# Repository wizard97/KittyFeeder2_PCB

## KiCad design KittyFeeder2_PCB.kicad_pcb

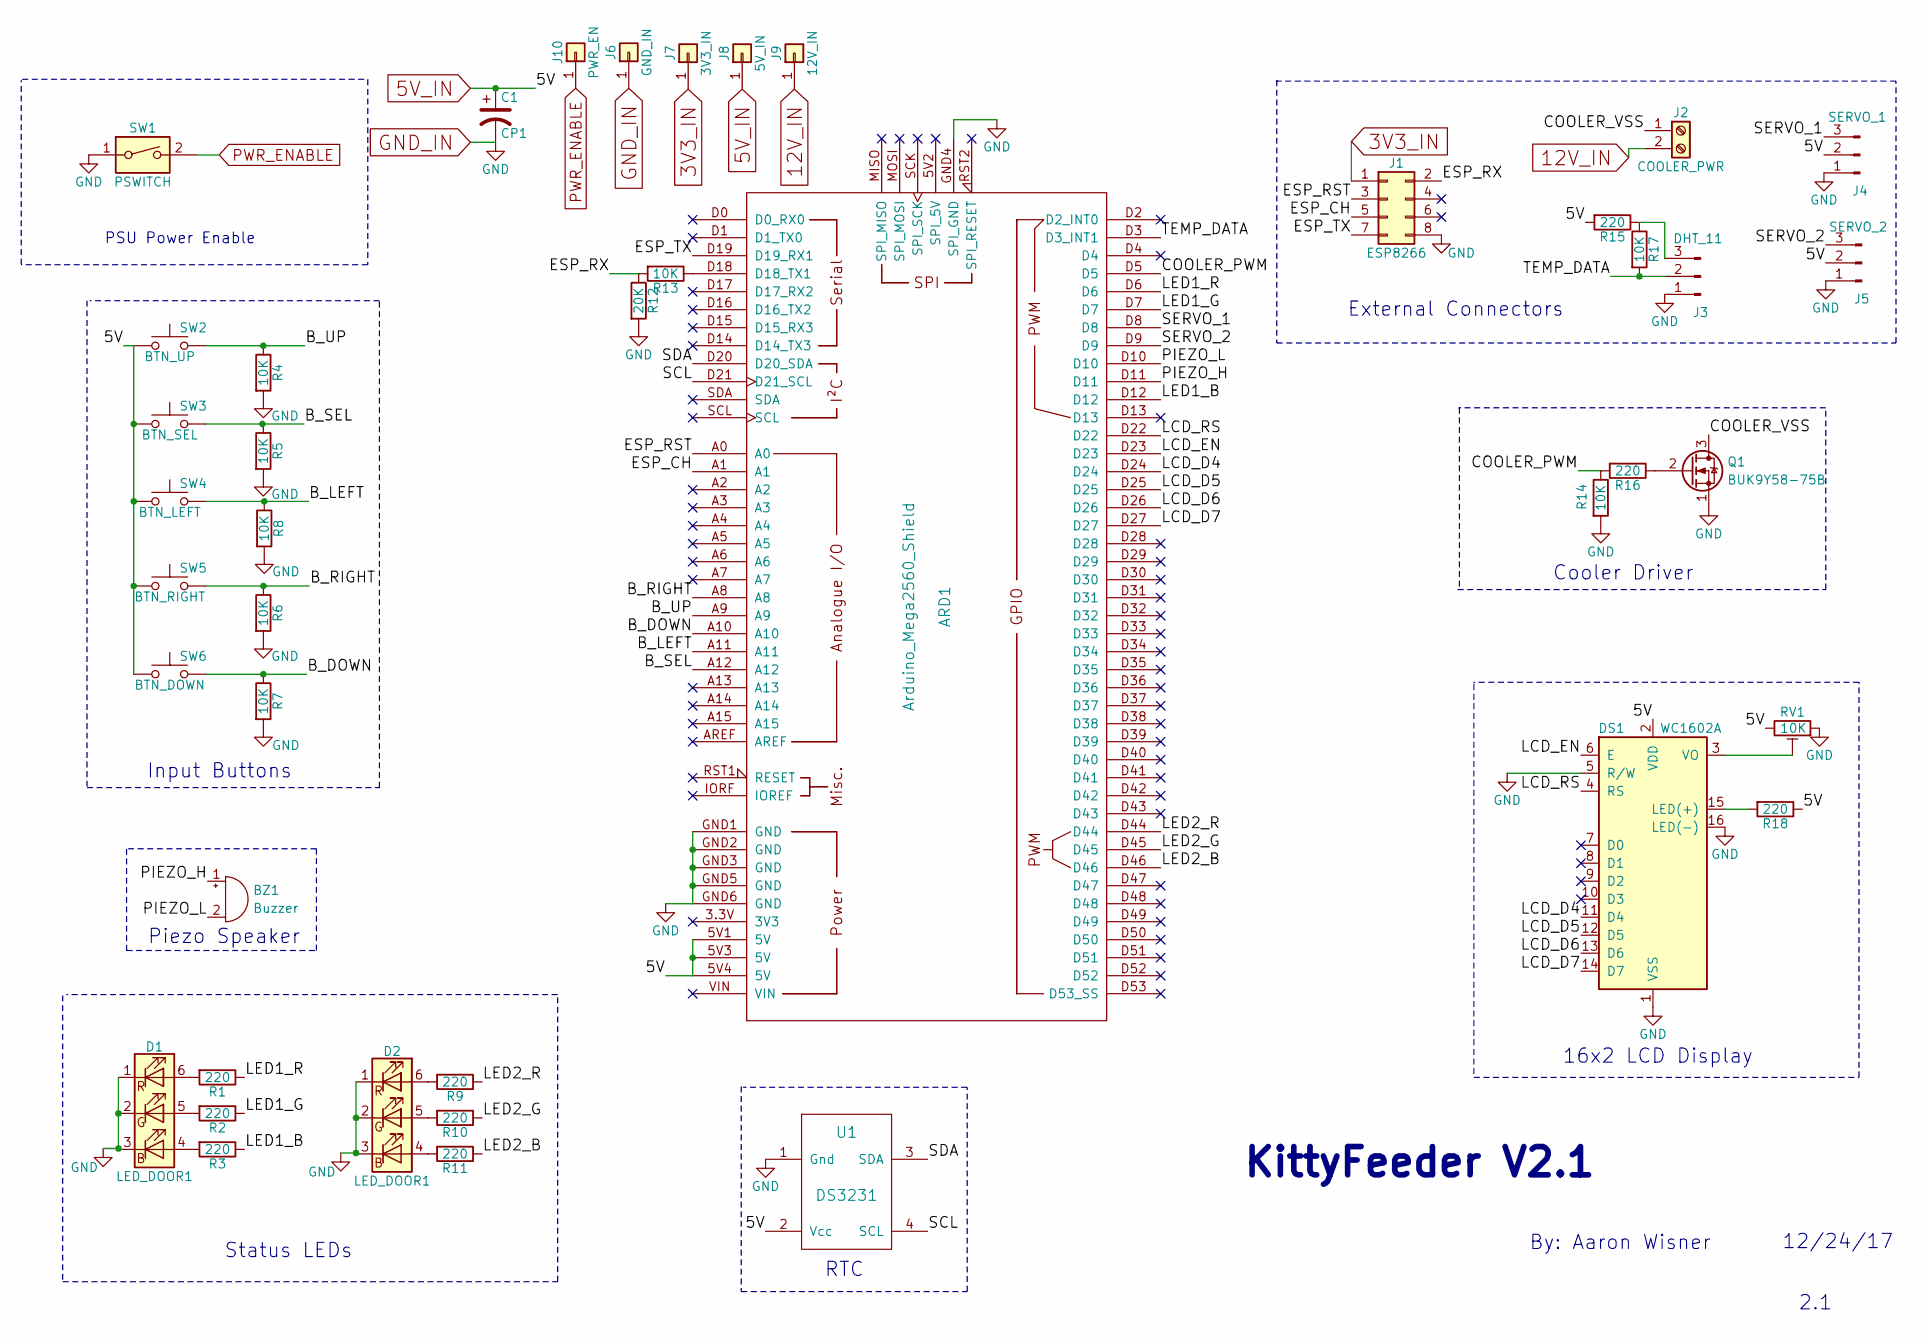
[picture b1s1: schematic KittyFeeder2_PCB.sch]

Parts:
ARD1: Arduino_Mega2560_Shield
BZ1: Buzzer; Buzzer_12x9.5RM7.6
C1: CP1; CP_Radial_D8.0mm_P2.50mm
D1, D2: LED_DOOR1; LED_RGB_PLCC-6
DS1: WC1602A
J1: ESP8266; Socket_Strip_Straight_2x04_Pitch2.54mm
J2: COOLER_PWR; TerminalBlock_Phoenix_MKDS1.5-2pol
J3: DHT_11; Socket_Strip_Straight_1x03_Pitch2.54mm
J4: SERVO_1; Socket_Strip_Straight_1x03_Pitch2.54mm
J5: SERVO_2; Socket_Strip_Straight_1x03_Pitch2.54mm
J6: GND_IN; SolderWirePad_4xSquare_2mmDrill
J7: 3V3_IN; SolderWirePad_single_2mmDrill
J8: 5V_IN; SolderWirePad_2x_2mmDrill
J9: 12V_IN; SolderWirePad_4xSquare_2mmDrill
J10: PWR_EN; SolderWirePad_4xSquare_2mmDrill
Q1: BUK9Y58-75B; SOT-669_LFPAK
R1, R2, R3, R9, R10, R11, R15, R16, R18: 220; R_0603
R4, R5, R6, R7, R8, R13, R14, R17: 10K; R_0603
R12: 20K; R_0603
RV1: 10K; Potentiometer_WirePads_Small
SW1: PSWITCH; Socket_Strip_Straight_1x02_Pitch2.54mm
SW2: BTN_UP; SW_PUSH-12mm
SW3: BTN_SEL; SW_PUSH-12mm
SW4: BTN_LEFT; SW_PUSH-12mm
SW5: BTN_RIGHT; SW_PUSH-12mm
SW6: BTN_DOWN; SW_PUSH-12mm
U1: DS3231; Socket_Strip_Straight_1x04_Pitch2.54mm

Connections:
3V3_IN: J1.1, J7.1
5V_IN: ARD1.5V1 (5V), ARD1.5V3 (5V), ARD1.5V4 (5V), C1.1, DS1.2 (VDD), J4.2, J5.2, J8.1, R15.2, R18.1, RV1.3, SW2.1, SW3.1, SW4.1, SW5.1, SW6.1, U1.2 (Vcc)
12V_IN: J2.2, J9.1
/B_DOWN: ARD1.A10, R7.1, SW6.2
/B_LEFT: ARD1.A11, R8.1, SW4.2
/B_RIGHT: ARD1.A8, R6.1, SW5.2
/B_SEL: ARD1.A12, R5.1, SW3.2
/B_UP: ARD1.A9, R4.1, SW2.2
/COOLER_PWM: ARD1.D5, R14.1, R16.2
/COOLER_VSS: J2.1, Q1.3 (D)
/ESP_CH: ARD1.A1, J1.5
/ESP_RST: ARD1.A0, J1.3
/ESP_RX: J1.2, R12.1, R13.2
/ESP_TX: ARD1.D19 (D19_RX1), J1.7
/LCD_D4: ARD1.D24, DS1.11 (D4)
/LCD_D5: ARD1.D25, DS1.12 (D5)
/LCD_D6: ARD1.D26, DS1.13 (D6)
/LCD_D7: ARD1.D27, DS1.14 (D7)
/LCD_EN: ARD1.D23, DS1.6 (E)
/LCD_RS: ARD1.D22, DS1.4 (RS)
/LED1_B: ARD1.D12, R3.1
/LED1_G: ARD1.D7, R2.1
/LED1_R: ARD1.D6, R1.1
/LED2_B: ARD1.D46, R11.1
/LED2_G: ARD1.D45, R10.1
/LED2_R: ARD1.D44, R9.1
/PIEZO_H: ARD1.D11, BZ1.1 (-)
/PIEZO_L: ARD1.D10, BZ1.2 (+)
/SCL: ARD1.D21 (D21_SCL), U1.4 (SCL)
/SDA: ARD1.D20 (D20_SDA), U1.3 (SDA)
/SERVO_1: ARD1.D8, J4.3
/SERVO_2: ARD1.D9, J5.3
/TEMP_DATA: ARD1.D3 (D3_INT1), J3.2, R17.2
GND_IN: ARD1.GND1 (GND), ARD1.GND2 (GND), ARD1.GND3 (GND), ARD1.GND4 (SPI_GND), ARD1.GND5 (GND), ARD1.GND6 (GND), C1.2, D1.1 (RK), D1.2 (GK), D1.3 (BK), D2.1 (RK), D2.2 (GK), D2.3 (BK), DS1.1 (VSS), DS1.5 (R/W), DS1.16 (LED(-)), J1.8, J3.1, J4.1, J5.1, J6.1, Q1.1 (S), R4.2, R5.2, R6.2, R7.2, R8.2, R12.2, R14.2, RV1.1, SW1.1, U1.1 (Gnd)
unnamed: ARD1.D18 (D18_TX1), R13.1
unnamed: D1.4 (BA), R3.2
unnamed: D1.5 (GA), R2.2
unnamed: D1.6 (RA), R1.2
unnamed: D2.4 (BA), R11.2
unnamed: D2.5 (GA), R10.2
unnamed: D2.6 (RA), R9.2
unnamed: DS1.3 (VO), RV1.2
unnamed: DS1.15 (LED(+)), R18.2
unnamed: J3.3, R15.1, R17.1
unnamed: Q1.2 (G), R16.1
PWR_ENABLE: J10.1, SW1.2

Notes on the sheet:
PSU Power Enable
KittyFeeder V2.1
By: Aaron Wisner
2.1
12/24/17
Input Buttons
Status LEDs
RTC
Piezo Speaker
16x2 LCD Display
Cooler Driver
External Connectors

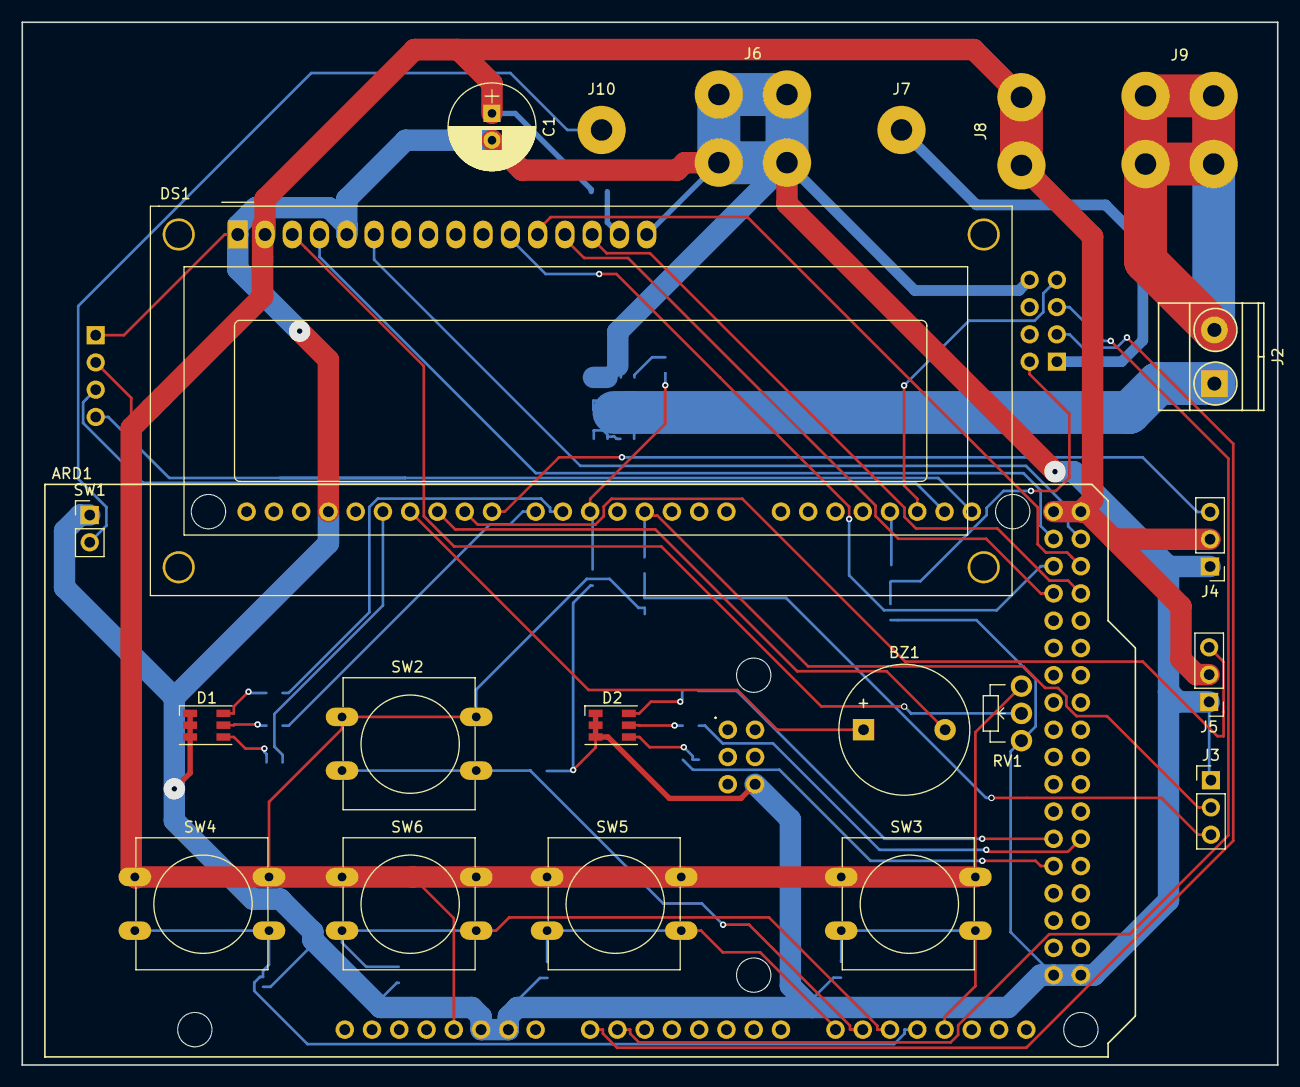
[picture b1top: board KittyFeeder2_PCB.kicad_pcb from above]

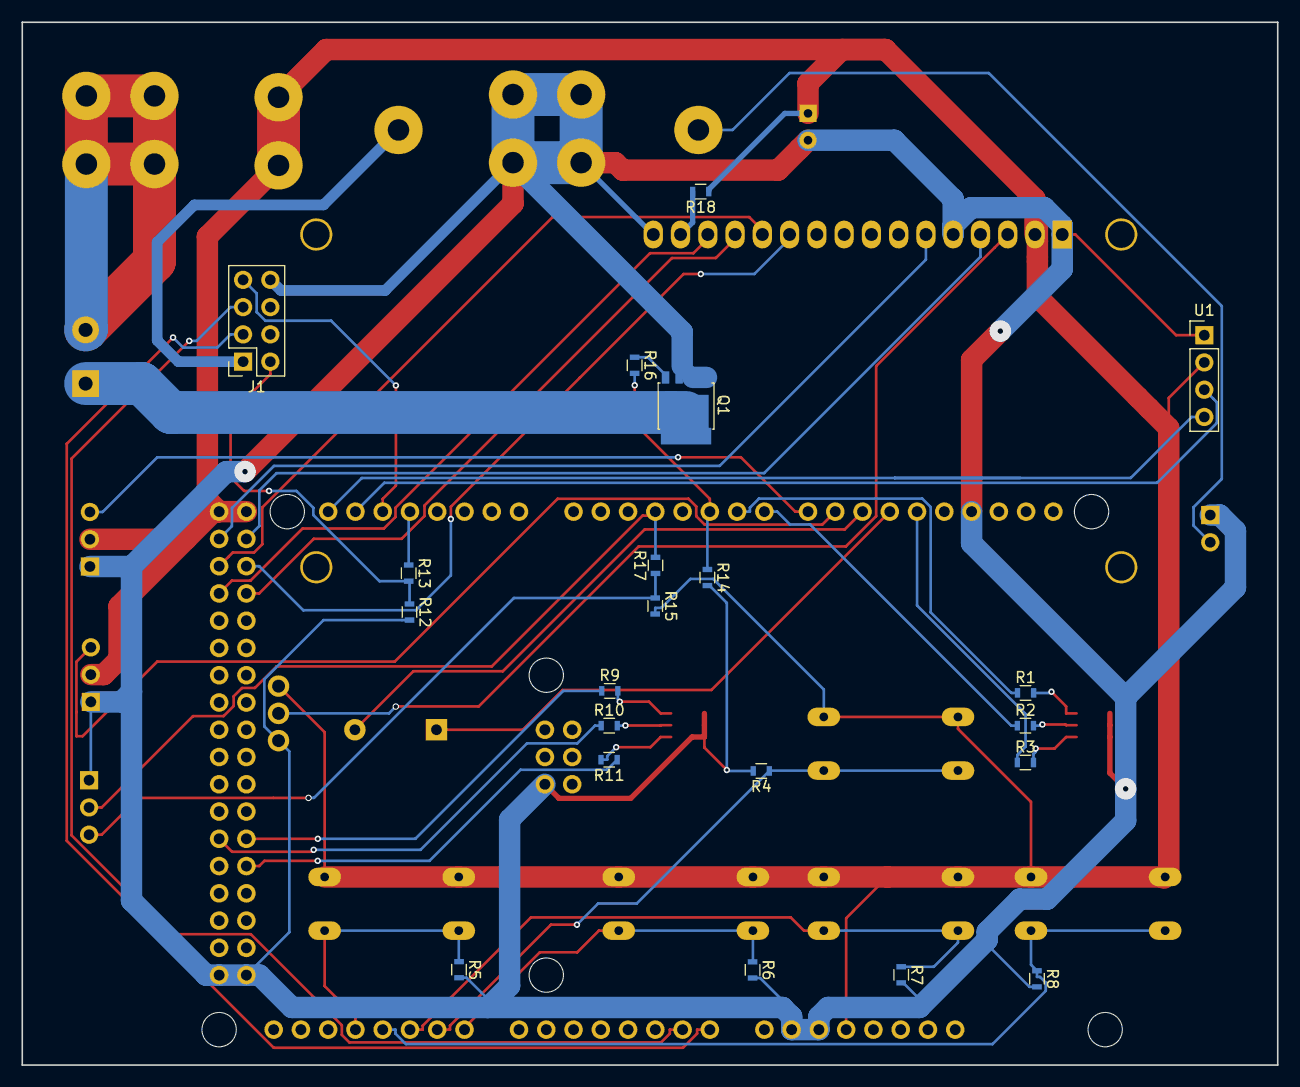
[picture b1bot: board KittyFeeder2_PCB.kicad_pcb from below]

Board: 2 copper layers, 117.0 x 97.2 mm, 43 parts (21 on the bottom side), 46 nets.

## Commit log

2017-12-25 :octocat: Added .gitattributes & .gitignore files
2017-12-25 More routing
2017-12-25 Let autorouter rip
2017-12-25 passing drc
